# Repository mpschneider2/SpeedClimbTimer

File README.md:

# SpeedClimbTimer

How it should work: holding button 1 for 5 seconds sets the clock to 0, releasing the long hold (onebutton) after the 5 seconds starts the timer
Hitting button 2 should pause the timer and it should blink slowly if not a high score, strobe if a high score. Maybe add a buzzer

it should continue blinking until button 1 is pressed/clicked, where it should then show the high score in solid light.

And a quadruple click should erase the last record if it was made in the same session in which it was plugged in.

and every time a new record is made, in needs to be stored in the EEPROM

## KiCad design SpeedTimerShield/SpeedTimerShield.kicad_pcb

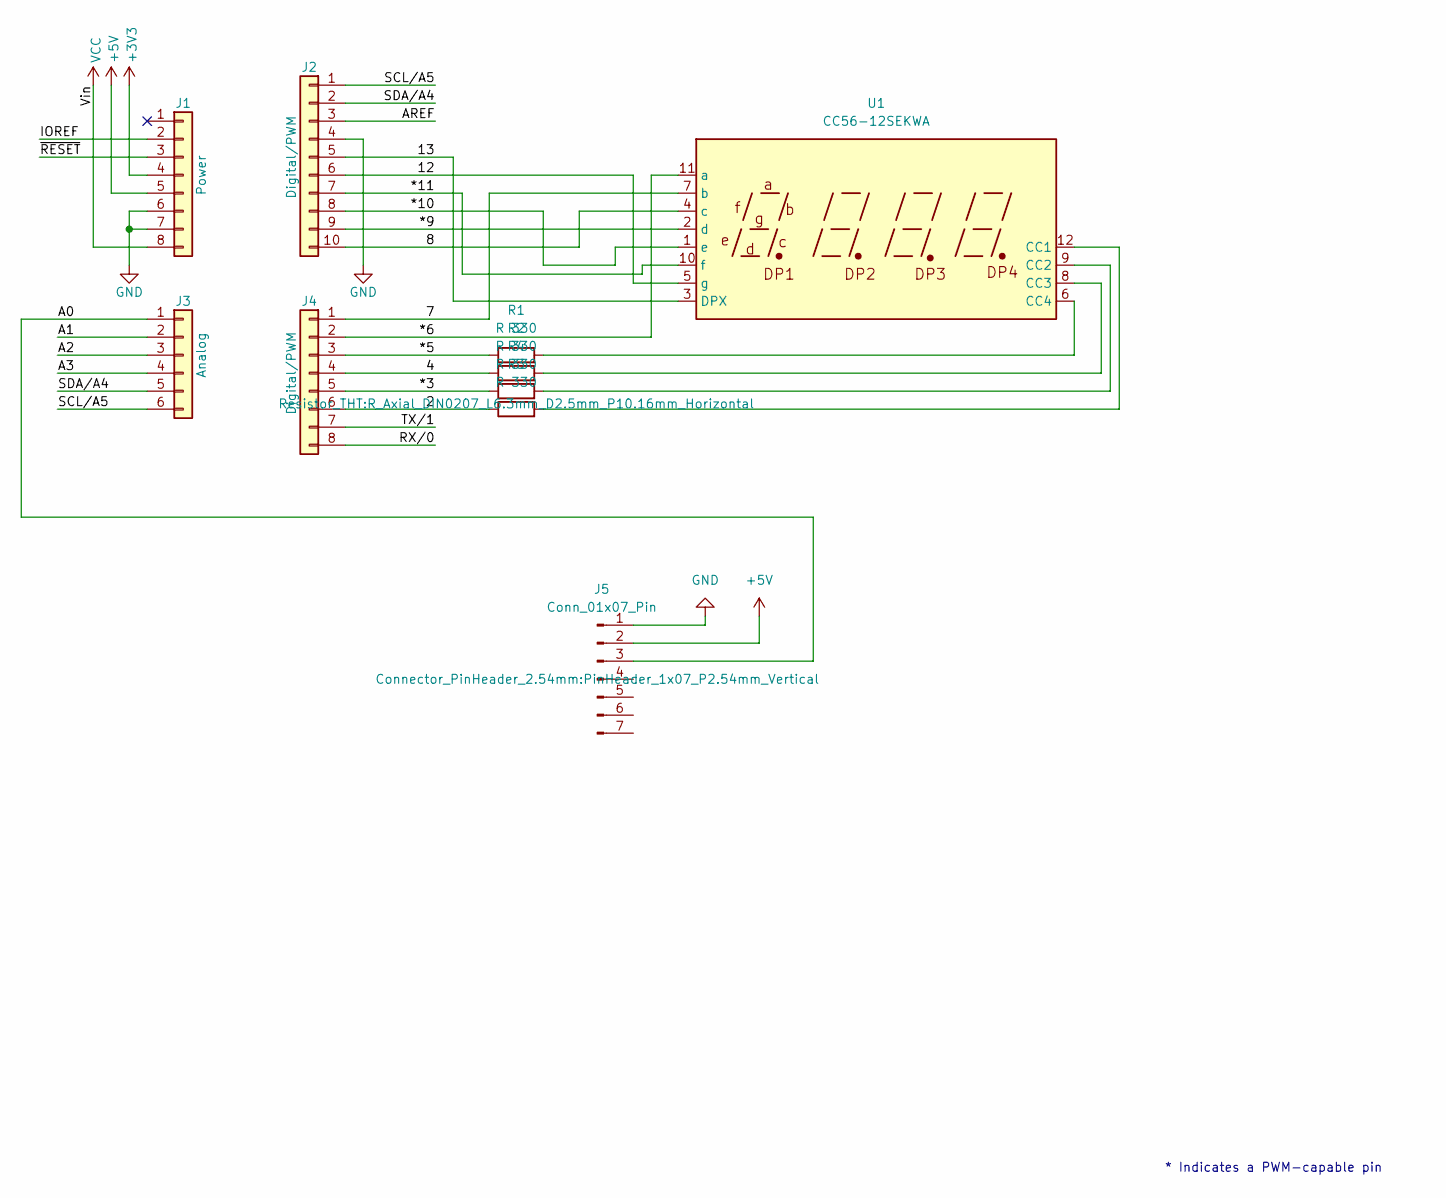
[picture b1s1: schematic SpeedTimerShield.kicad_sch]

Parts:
J1: Power; PinSocket_1x08_P2.54mm_Vertical
J2: Digital/PWM; PinSocket_1x10_P2.54mm_Vertical
J3: Analog; PinSocket_1x06_P2.54mm_Vertical
J4: Digital/PWM; PinSocket_1x08_P2.54mm_Vertical
J5: Conn_01x07_Pin; PinHeader_1x07_P2.54mm_Vertical
R1, R2, R3, R4: R 330; R_Axial_DIN0207_L6.3mm_D2.5mm_P10.16mm_Horizontal
U1: CC56-12SEKWA; CA56-12SEKWA

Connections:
+3V3: J1.4
+5V: J1.5, J5.2
/2: J4.6, R3.1
/4: J4.4, R2.1
/7: J4.1, U1.7 (b)
/8: J2.10, U1.4 (c)
/12: J2.6, U1.5 (g)
/13: J2.5, U1.3 (DPX)
/*3: J4.5, R4.1
/*5: J4.3, R1.1
/*6: J4.2, U1.11 (a)
/*9: J2.9, U1.2 (d)
/*10: J2.8, U1.1 (e)
/*11: J2.7, U1.10 (f)
/A0: J3.1, J5.3
/A1: J3.2
/A2: J3.3
/A3: J3.4
/AREF: J2.3
/IOREF: J1.2
/RX/0: J4.8
/SCL/A5: J2.1, J3.6
/SDA/A4: J2.2, J3.5
/TX/1: J4.7
/~RESET: J1.3
GND: J1.6, J1.7, J2.4, J5.1
unnamed: R3.2, U1.12 (CC1)
unnamed: R4.2, U1.9 (CC2)
unnamed: R2.2, U1.8 (CC3)
unnamed: R1.2, U1.6 (CC4)
VCC: J1.8

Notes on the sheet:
* Indicates a PWM-capable pin

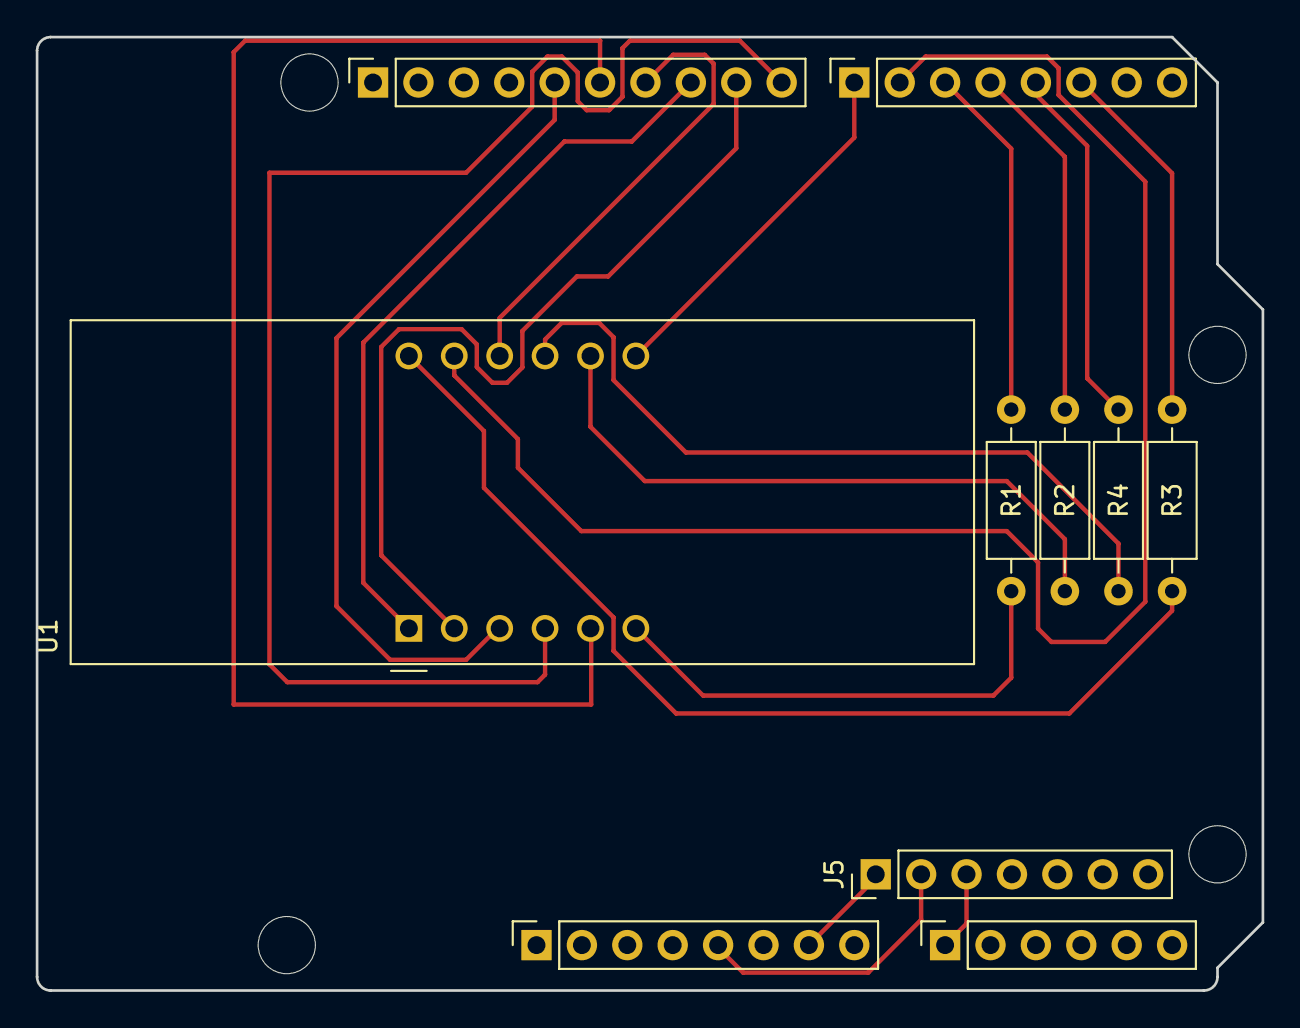
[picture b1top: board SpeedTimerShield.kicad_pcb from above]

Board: 2 copper layers, 68.6 x 53.3 mm, 14 parts (0 on the bottom side), 21 nets.

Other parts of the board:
MH1, MH2, MH3, MH4: MountingHole_3.2mm

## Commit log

2024-12-03 initial increase count
2024-12-03 readme
2024-12-03 how it should work as an end user
2024-12-04 most features except saving and restoring old times
2025-01-19 full working shield v1
